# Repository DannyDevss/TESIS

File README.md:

# TESIS — Workspace ROS 2 del UGV de rescate (RMD)

Workspace de **ROS 2 Jazzy** para un vehículo terrestre no tripulado (UGV) de
rescate con **orugas y flippers articulados**. Incluye el puente con el hardware
de motores, la odometría, la fusión sensorial (EKF), el modelo del robot (URDF)
y la inferencia de la política de flippers entrenada por refuerzo en el PC.

```bash
cd ~/TESIS && git checkout PRINCIPAL
colcon build --packages-select ugv_bridge && source install/setup.bash
ros2 launch ugv_bridge can_studio.launch.py   # simulación CAN + espía + Foxglove
```

Después, conectar Foxglove a `ws://localhost:8765` y cargar el layout
`src/ugv_bridge/config/ugv_control_v4.json`. **Foxglove es la única interfaz**:
no hay RViz ni ventanas Qt en ningún launch.

## Paquete (`src/`)

| Paquete | Rol | Ejecutables |
|---------|-----|-------------|
| **ugv_bridge** | Todo: puente ROS ↔ motores (orugas + flippers), IMU, odometría, EKF, URDF, launch, espía del bus CAN e inferencia de la política | `flipper_node`, `track_odometry_node`, `teleop_flippers`, `can_monitor`, `politica_flippers`, `motor_emulator`, `pi3hat_imu`, `esp32_bridge`, `gui_a_comandos` *(legado)* |

**Un solo paquete, a propósito.** El workspace tenía además `ugv_core`,
`ugv_sim`, `ugv_policy` y `ugv_msgs`, de una versión anterior del proyecto que
modelaba navegación 2D plana: telémetros, `/cmd_vel` y tres acciones discretas.
Esa no es la tarea de la tesis. Este robot tiene orugas y flippers articulados
y se comanda por `/cmd_tracks` y `/cmd_flippers`, y no había nada que conectara
lo uno con lo otro. Se eliminaron en octubre de 2026 para que no quedara código
muerto con apariencia de sistema. Lo único que se rescató de ellos es la
inferencia de la política, que ahora vive en `ugv_bridge`.

## Arquitectura del track de flippers (`ugv_bridge`)

```
Foxglove (paneles Publish y Teleop)  /  política RL
   │  /cmd_tracks (vel. orugas)   /cmd_flippers (pos. flippers)
   ▼
flipper_node  ──►  RMD_Hardware (real pi3hat/CAN  o  gemelo digital)
   │  /joint_states   /imu/data_raw
   ├──► track_odometry_node ──► /odom ─┐
   │                                   ├──► EKF (robot_localization) ──► /odometry/filtered + TF
   └──► robot_state_publisher (URDF) ──► TF de cada flipper ──► Foxglove
```

- **8 motores**: IDs 1–4 orugas (comando de velocidad), IDs 5–8 flippers (comando de posición).
- **Flippers**: juntas `continuous`, giran **360°** sin topes.
- **Sim-to-real**: el mismo nodo sirve para simulación y hardware; solo cambia el
  parámetro `modo_simulacion`. El modo hardware real (pi3hat + CAN + IMU) queda como TODO.

## Geometría del robot: una sola fuente de verdad

Todas las dimensiones físicas (posición de los motores de flipper, largo del
flipper, radio de las ruedas, radio y separación de las orugas, montaje de la IMU)
viven en **[`src/ugv_bridge/config/geometria_robot.yaml`](src/ugv_bridge/config/geometria_robot.yaml)**.
De ahí las leen, sin duplicar un solo número:

```
config/geometria_robot.yaml          <-- editar SOLO aquí
        |
        +--> urdf/ugv.urdf.xacro     (xacro.load_yaml)  --> modelo 3D, colisiones, TF
        +--> track_odometry_node     (radio/ancho de orugas)
        +--> flipper_node / driver   (IMU sintética, montaje de la IMU)
```

Cuando lleguen las medidas reales del chasis:

```bash
# 1. Editar config/geometria_robot.yaml
# 2. Refrescar el URDF plano (para Foxglove y herramientas que no procesan xacro)
bash src/ugv_bridge/scripts/generar_urdf.sh
# 3. Recompilar
colcon build
```

Los launch procesan el `.xacro` en caliente, así que el modelo **nunca** queda
desfasado del YAML. El `.urdf` plano es un artefacto generado: no editarlo a mano.

## Compilar

```bash
cd ~/Proyectos/ugv_ws
colcon build
source install/setup.bash
```

## Uso rápido

> **La única interfaz es Foxglove.** Ningún launch abre RViz ni ventanas Qt: la
> GUI de sliders y la vieja ventana de `can_monitor` publicaban en los mismos
> tópicos de comando que Foxglove y se pisaban entre sí (`flipper_node` retiene
> el último comando que recibe). Todos los launch levantan el puente WebSocket
> en el 8765; conecta con `ws://localhost:8765` y el layout
> `config/ugv_control_v4.json`.

```bash
# Posar el robot (gemelo digital), sin locomoción:
ros2 launch ugv_bridge view.launch.py

# Sistema completo (driver + odometría + EKF + Foxglove):
ros2 launch ugv_bridge flipper.launch.py use_ekf:=true

# Simulación con tramas CAN reales sobre vcan0, y con espía del bus:
ros2 launch ugv_bridge can_view.launch.py
ros2 launch ugv_bridge can_studio.launch.py

# Matar ventanas/publicadores huérfanos de una sesión vieja:
bash src/ugv_bridge/scripts/limpiar_fantasmas.sh

# Mover (un solo mensaje basta; el nodo retiene el último comando):
ros2 topic pub --once /cmd_flippers std_msgs/msg/Float64MultiArray "{data: [0.78,0.78,0.78,0.78]}"
ros2 topic pub --once /cmd_tracks   std_msgs/msg/Float64MultiArray "{data: [5.0,5.0,5.0,5.0]}"

# Política de flippers, solo observando las señales táctiles (no comanda nada):
ros2 launch ugv_bridge flipper.launch.py use_politica:=true
```

> ⚠️ Usa `--once`, no `-r`. La velocidad de las orugas es persistente: para frenar,
> publica explícitamente `[0,0,0,0]` en `/cmd_tracks`.

## RL: se entrena en el PC, se ejecuta en la Raspberry

El entrenamiento **no** corre en la Pi. En el robot solo va un archivo `.onnx`
ya entrenado, que ejecuta `politica_flippers` con `onnxruntime`. La Pi no
necesita gymnasium, ni stable-baselines3, ni torch.

```
PC de alta gama                          Raspberry Pi
---------------                          ------------
simulador + RL (PPO/SAC)                 politica_flippers
        |                                  lee /joint_states, /imu/data_raw
        v                     .onnx        construye la observación
scripts/exportar_onnx.py  ──────────────▶  ejecuta la red (onnxruntime)
                          .json            publica /cmd_flippers y /cmd_tracks
```

La política la entrena un profesor y es **autónoma**: maneja flippers y orugas.
Su **contrato** (qué es cada número que entra y sale de la red) viaja en el
`.json` junto al modelo, y el robot arma la observación a partir de él: así no
puede desincronizarse con el simulador. El formato está en
`ugv_bridge/contrato_politica.py`; los frenos (desactivada al arrancar,
watchdog, topes duros y parada segura con orugas a 0), en
`ugv_bridge/ejecutor_politica.py`. Para probar sin modelo real:
`scripts/modelo_falso.py`.

Detalle completo del objetivo (percepción táctil sin sensor táctil), de las
señales y de los frenos de seguridad en `COMO_EJECUTAR.md`, sección 3.

## Documentación

- **[COMO_EJECUTAR.md](COMO_EJECUTAR.md)** — runbook detallado (entornos, launch, tópicos, inspección).
- **[DEFENSA_ROS2.txt](DEFENSA_ROS2.txt)** — guía de preguntas/respuestas de ROS 2 para la defensa.
- **[BITACORA_2026-07-11.txt](BITACORA_2026-07-11.txt)** — bitácora de construcción del track de flippers.

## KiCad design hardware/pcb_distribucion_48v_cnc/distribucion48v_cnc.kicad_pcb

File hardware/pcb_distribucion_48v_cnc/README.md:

# Distribución de 48 V — versión para la CNC del laboratorio

El circuito es el mismo de [`../pcb_distribucion_48v`](../pcb_distribucion_48v/README.md):
XT60 de batería, 8 salidas XT30 con fusible 5×20, una salida auxiliar de 48 V con
fusible y sensado con PTC. Cambia el cobre, para poder
fresarla en la **Bungard CCD** del laboratorio (manual en `../CNCFABLAB/`).

## Qué cambia respecto de la placa para fabricante

| | Fabricante (`pcb_distribucion_48v`) | CNC (esta) |
|---|---|---|
| Caras de cobre | 2 (48 V arriba, GND abajo) | **1, la de abajo (lado de soldadura)** |
| Cobre | 2 oz (70 µm) | **1 oz (35 µm)**, el de las placas vírgenes comunes |
| Metalizado de agujeros | sí | **no**: la CCD no metaliza |
| Serigrafía / máscara | sí | no; los rótulos `M1`…`M8` van fresados en el cobre |
| Taladro de los clips | 1.3 mm | **1.4 mm**, el mismo de las borneras: una broca menos |
| Tamaño, agujeros M3 | 104 × 84 mm | igual: se atornilla en el mismo lugar |

**Por qué una sola cara:** sin metalizado, un pad solo conecta en la cara donde se
suelda. Los XT60 y XT30 van verticales con el cuerpo apoyado en la cara de arriba, así
que un pad de arriba quedaría tapado y no se podría soldar. Todo el cobre va abajo,
donde se sueldan todas las patas.

**Cómo entra en una cara:** GND rellena todo lo que no es otra red. Queda un anillo
por el borde que toca los `-` del XT60, de los ocho XT30 y de las borneras. Adentro
van el bus de 48 V (franja central), los planos `OUT1`…`OUT8` (uno por canal, del
fusible al `+` de su XT30), el plano `AUX48V` (de F10 a J11, igual que un canal más) y
la pista de sensado (del PTC a J10). Nada se cruza. El DRC da **0 sin conectar**.

## Archivos

| Archivo | Qué es |
|---|---|
| `fabricacion/distribucion48v_cnc-B_Cu.gbl` | Cobre (cara **de abajo**). Gerber RS-274X, sin atributos X2. |
| `fabricacion/distribucion48v_cnc-Edge_Cuts.gm1` | Contorno de la placa. |
| `fabricacion/distribucion48v_cnc.drl` | Taladros, Excellon en mm, un solo archivo (64 agujeros, 5 diámetros). |
| `montaje_1a1.pdf` | Vista de arriba a **escala 1:1**: para imprimir y comprobar los conectores. |
| `preview.png` | Cara de arriba con el cobre de abajo visto por transparencia. |
| `cobre_lado_soldadura.png` | El cobre visto desde abajo, como queda la placa fresada. |
| `gen.py` | Fuente: `python3 gen.py` regenera todo. |
| `centrar_pdf.py` | Centra la placa en `montaje_1a1.pdf` (kicad-cli la deja en la esquina). |

Los componentes son los mismos de la otra placa: ver su `bom.csv` y `COMPRAS.md`.
Además hace falta **una placa virgen FR4 de 1.6 mm, una cara, 35 µm**, de al menos
125 × 95 mm. La Eurocard de 160 × 100 sirve, y sobra espacio para un intento más.

## En la CCD, paso a paso

Basado en el manual de la Bungard CCD (RoutePro3000). Los números de página son los
del manual.

### 1. Poner la placa

- **Cobre hacia arriba.** La fresa trabaja desde arriba. Los componentes van después
  en la otra cara, la sin cobre.
- Debajo, una **placa de sacrificio** (MDF o la "drill backing board" del
  laboratorio) más grande que la virgen, fija a la mesa con las bridas. Así las
  brocas y la fresa de contorno la atraviesan sin tocar la mesa de aluminio (p. 24).
- La placa virgen va pegada a la de sacrificio con **cinta doble faz**, bien plana y
  sin burbujas. Con una sola cara no hacen falta pines de referencia (p. 24–25). Si
  la placa se curva, la aislación sale más honda en unas partes que en otras.
- Ubicarla a unos **5 mm del cero de la máquina**, en la esquina de adelante a la
  izquierda, con un borde alineado con el eje X o Y (p. 17 y 20).
- En el software, cargar el **espesor real** de la placa (1.6 mm) y el de la de
  sacrificio (p. 20).

### 2. Cargar los archivos

En RoutePro3000/IsoCam: el `.drl` como taladros, el `B_Cu.gbl` como **capa de abajo**
y el `Edge_Cuts.gm1` como contorno. El gerber está visto desde arriba, como todo
gerber: al marcarlo como capa de abajo, el software lo espeja. **Comprobar en
pantalla que los rótulos `M1`…`M8` se leen al derecho en la vista de abajo**: si se
leen espejados, la placa sale al revés.

### 3. Fresar, y cuándo cambiar de herramienta

Son **5 herramientas** y se usan en este orden (p. 21). Cada fila es un cambio: se
termina todo lo de esa herramienta antes de pasar a la siguiente.

| Cuándo | Herramienta | Qué hace |
|---|---|---|
| 1. Al empezar, capa de taladros | broca **0.8 mm** | los 2 agujeros del PTC (F9) |
| 2. Cuando termina la 0.8 | broca **1.4 mm** | los 40 agujeros de clips y borneras |
| 3. Cuando termina la 1.4 | broca **2.7 mm** | los 16 agujeros de los XT30 |
| 4. Terminados los taladros, se cambia a la capa de aislación | fresa de aislación **0.5 mm** (o la V que tengan) | separa las redes en el cobre |
| 5. Terminada la aislación, se cambia a la capa de contorno | fresa de contorno **2.0 mm** | XT60 (4.5 mm) y M3 (3.2 mm) como círculos, y al final el borde de la placa con puentes |

Cómo se hace cada cambio depende de la máquina:

- **Con cambiador automático (ATC)**, la barra de portaherramientas al frente:
  antes de empezar se ponen las 5 herramientas en los puestos que pide el software,
  con el **puesto 0 libre** para el pin de prueba. Al dar Start, la máquina mide
  cada una y las cambia sola (p. 19–21).
- **Manual (MTC o sin cambiador):** al terminar con una herramienta, el eje Z sube y
  el software pide la siguiente. Se cambia **con el husillo detenido**: apretar el
  botón de arriba del husillo, girar hasta que trabe, soltar la pinza (p. 19). Después
  de poner la nueva, OK.

En cualquiera de los dos casos:

- **Todas las herramientas con el anillo de tope** a 21 mm de la punta (p. 11). Con
  él la máquina sabe el largo; sin él, puede clavar la herramienta en la mesa.
- **No tocar la herramienta con el husillo girando**; esperar a que se detenga (p. 9).
- **Para la aislación, el limitador de profundidad** (el patín verde alrededor de la
  fresa): corta siempre lo justo aunque la placa no esté perfecta (p. 21–22).
  Con ATC, la abertura del patín mira hacia los portaherramientas; si no, choca en
  el cambio (p. 22).
- **Antes de la aislación completa, probar la profundidad** en un trazo que no
  importe, por ejemplo el contorno exterior, como sugiere el manual: tiene que
  cortar el cobre y apenas marcar la fibra. Si queda cobre, bajar el limitador un
  punto (cada punto son 50 µm). Mejor que quede alto que hondo (p. 22).

### 4. Después de fresar

Antes de soldar, con el multímetro en continuidad, medir que **no** suene entre GND,
VBAT, AUX48V, SENSE y cada OUT. Una rebaba o una tira de cobre que no se fresó deja un corto a
48 V.

### Herramientas y parámetros (FR4, tablas del manual)

| Paso | Herramienta | Diámetro | Avance XY | RPM | Avance Z | Página |
|---|---|---|---|---|---|---|
| Taladro (PTC, 2) | broca estándar | 0.8 mm | 2200 mm/min | 63 000 | — | 29 |
| Taladro (clips y borneras, 40) | broca estándar | 1.4 mm | 2800 mm/min | 63 000 | — | 29 |
| Taladro (XT30, 16) | broca estándar | 2.7 mm | 1800 mm/min | 45 400 | — | 29 |
| Agujeros M3 (3.2 mm, 4) y XT60 (4.5 mm, 2) | ver abajo | | | | | 29 |
| Aislación | fresa de un filo (micro cutter) | 0.5 mm | 100–200 mm/min | 63 000 | 200 mm/min | 31 |
| Contorno | fresa SC/FT | 2.0 mm | 1000 mm/min | 38 800 | 1300 mm/min | 32 |

- **Agujeros de más de 3 mm:** el manual recomienda pretaladrar con 1.7 mm desde
  3.0 mm. Con el diámetro máximo recomendado de 3.175 mm, lo más simple es que
  RoutePro/IsoCam los **frese como círculo** con la fresa de contorno. Si el
  laboratorio tiene broca de 3.2 y de 4.5, también sirve.
- **Ancho de aislación: 1 mm.** Las redes están separadas 1 mm en el diseño. Para
  48 V sin barniz, IPC-2221 pide **al menos 0.6 mm**: una sola pasada de una fresa
  de 0.2–0.4 mm **no alcanza**. Pedir en IsoCam un ancho de aislación de 1 mm, por
  ejemplo dos pasadas de 0.5 mm, o una fresa de 1 mm.
- **Contorno con puentes** (p. 25) para que la placa no salte al final del corte.

## Corriente con cobre de 1 oz

Anchos en el punto más estrecho. Capacidad según IPC-2221, capa externa, con 20 °C de
subida de temperatura.

| Tramo | Ancho | Aguanta | Lleva (motores a ~3 A) |
|---|---|---|---|
| Plano por canal `OUTn` | 5 mm (junto al `-` del XT30) | ~10 A | 3 A (6 A nominal del driver) |
| Franja de GND arriba / abajo | 8.5 mm | ~15 A | 4 canales: ~12 A |
| Bus de 48 V | 21 mm | ~29 A | 8 canales: ~24 A |

Alcanza para lo que se pidió, con poco margen en las franjas de GND. Si se quiere más
margen, o si el cobre se oxida: **estañar** el bus, las franjas de GND y los planos
`OUT` (una capa de estaño suma sección), o soldar encima un alambre de cobre de
1.5 mm² a lo largo del bus y de las franjas.

## Después de fresar

- **No tiene máscara**: el cobre queda al aire. Estañarlo o pasarle barniz (laca
  para PCB, en spray) después de soldar. El barniz además mejora la aislación de 48 V.
- **Rótulos**: los `M1`…`M8`, `AUX` (salida de 48 V, J11) y `SEN` (sensado, J10) en
  cobre se leen desde abajo. Arriba no hay
  serigrafía: marcar con plumón permanente los IDs de motor junto a cada XT30, y
  `+`/`-` en el XT60 y las borneras, usando `montaje_1a1.pdf` de guía.
- Los pads de potencia van **sin thermal relief**, conectados de lleno al plano: se
  sueldan con un cautín de 60–80 W y punta gruesa. Con 1 oz cuesta menos que con
  2 oz.
- Al soldar los XT30/XT60, que el cuerpo quede **apoyado y recto** sobre la placa:
  sin metalizado, el pad de cobre es lo único que sujeta la pata. Si se
  tira del cable, se puede levantar el pad. Asegurar los cables con amarras al chasis.

## Antes de ir al laboratorio

- [ ] **Polaridad de los XT** (sigue pendiente, ver `../pcb_distribucion_48v/PENDIENTES.md`):
      imprimir `montaje_1a1.pdf` **al 100 %, sin "ajustar a la página"**, medir que
      la placa mida 104 × 84 mm en el papel, y poner encima un XT60 y un XT30 reales:
      el `-` moldeado en el cuerpo tiene que caer en el pad marcado `-`.
- [ ] Con el mismo papel, comprobar que las patas de los **clips 445-030** caen en los
      agujeros (dos patas a 5.2 mm, clip a clip 20.5 mm).
- [ ] Preguntar en el laboratorio:
  - ¿Tienen **placa virgen de una cara**? Si solo hay de doble cara, el cobre de
        arriba tiene que salir entero, o por lo menos fresar un anillo alrededor de
        cada agujero. Si no, las patas de los conectores tocan ese cobre y quedan
        todas en corto entre sí.
  - ¿Qué **fresas y brocas** hay en el cambiador? Hacen falta las brocas de 0.8,
        1.4 y 2.7 mm, una fresa de aislación (0.5 mm o un V-cut) y una fresa de
        contorno de 2 mm.
  - ¿Usan **IsoCam** para generar la aislación desde el gerber?

## Regenerar

Necesita KiCad 10 (la API `pcbnew` de Python):

```
python3 gen.py
kicad-cli pcb drc --refill-zones --severity-all distribucion48v_cnc.kicad_pcb
kicad-cli pcb export gerbers --layers B.Cu,Edge.Cuts --no-x2 --no-netlist -o fabricacion/ distribucion48v_cnc.kicad_pcb
kicad-cli pcb export drill --format excellon --excellon-units mm --excellon-zeros-format decimal --drill-origin absolute -o fabricacion/ distribucion48v_cnc.kicad_pcb
kicad-cli pcb export pdf --layers F.Silkscreen,F.Fab,Edge.Cuts --mode-single --sp --black-and-white -o montaje_1a1.pdf distribucion48v_cnc.kicad_pcb
python3 centrar_pdf.py      # mueve la placa al centro del A4, sin cambiar la escala
```

Estado al generarla: DRC de KiCad 10.0.7 con **0 sin conectar** y 0 errores de
cobre. Quedan 36 avisos `silk_over_copper` (serigrafía sobre pads): no importan,
porque la CCD no imprime serigrafía.

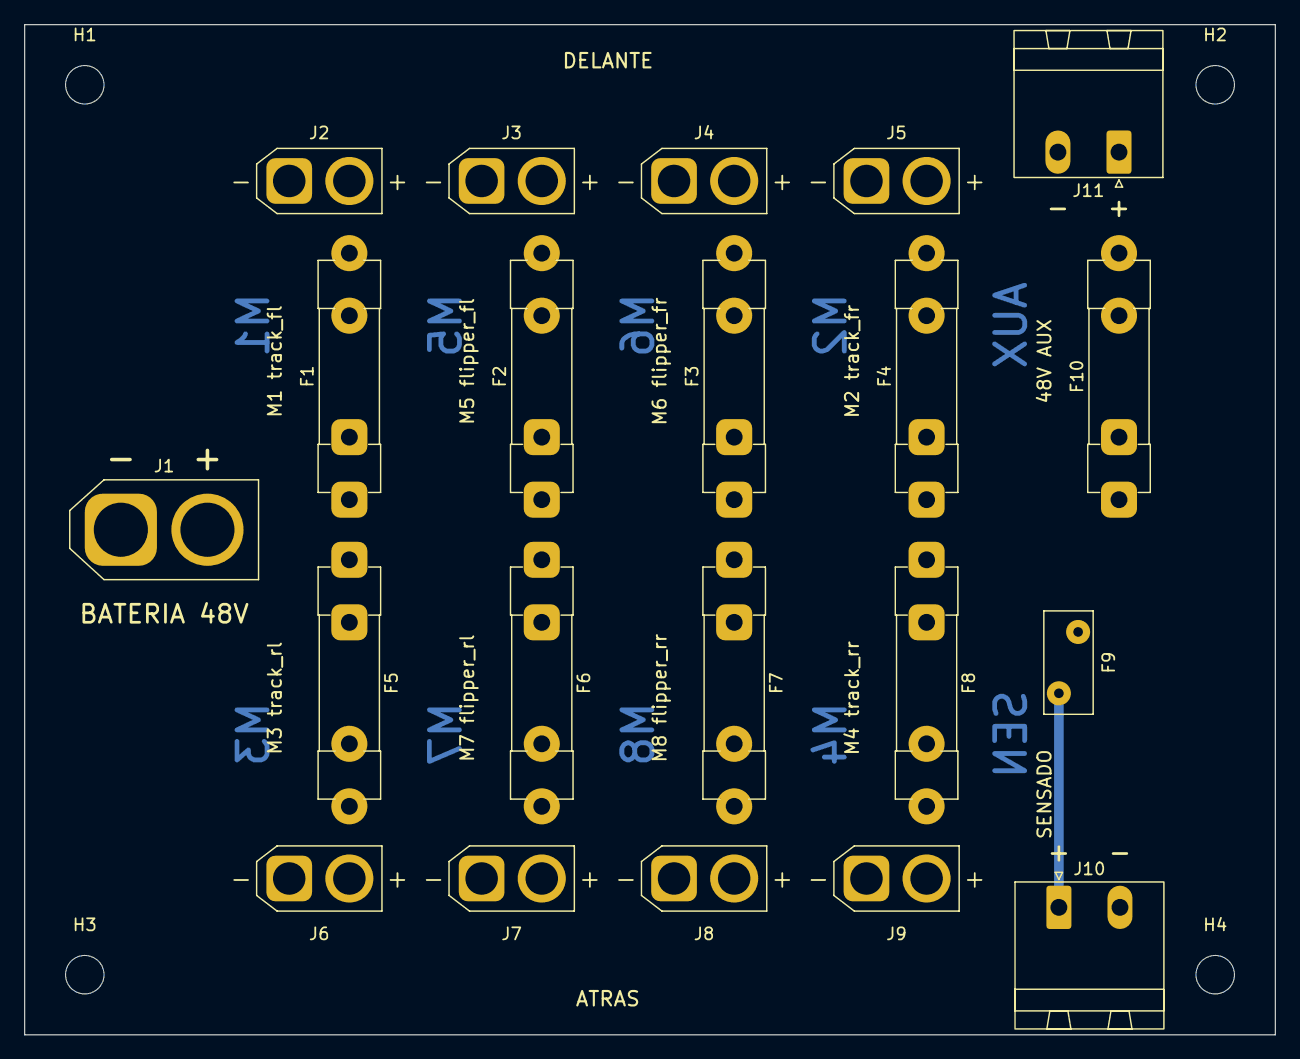
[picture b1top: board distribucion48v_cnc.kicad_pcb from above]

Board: 2 copper layers, 104.0 x 84.0 mm, 25 parts (0 on the bottom side), 12 nets.

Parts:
F1, F2, F3, F4, F5, F6, F7, F8: T10A 5x20; Fuseholder_Clip-5x20mm_Littelfuse_445-030_Inline_P20.50x5.2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
F9: 0ZRE0005FF; Fuse_BelFuse_0ZRE0005FF_L8.3mm_W3.8mm
F10: T2A 5x20; Fuseholder_Clip-5x20mm_Littelfuse_445-030_Inline_P20.50x5.2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
H1, H2, H3, H4: M3; MountingHole_3.2mm_M3
J1: XT60-M; AMASS_XT60-M_1x02_P7.20mm_Vertical
J2, J3, J4, J5, J6, J7, J8, J9: XT30U-F; AMASS_XT30U-F_1x02_P5.0mm_Vertical
J10: SENSADO; PhoenixContact_MSTBA_2,5_2-G-5,08_1x02_P5.08mm_Horizontal
J11: 48V AUX; PhoenixContact_MSTBA_2,5_2-G-5,08_1x02_P5.08mm_Horizontal

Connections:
AUX48V: F10.2, J11.1
GND: J1.1, J2.1, J3.1, J4.1, J5.1, J6.1, J7.1, J8.1, J9.1, J10.2, J11.2
OUT1: F1.2, J2.2
OUT2: F2.2, J3.2
OUT3: F3.2, J4.2
OUT4: F4.2, J5.2
OUT5: F5.2, J6.2
OUT6: F6.2, J7.2
OUT7: F7.2, J8.2
OUT8: F8.2, J9.2
SENSE: F9.2, J10.1
VBAT: F1.1, F2.1, F3.1, F4.1, F5.1, F6.1, F7.1, F8.1, F9.1, F10.1, J1.2

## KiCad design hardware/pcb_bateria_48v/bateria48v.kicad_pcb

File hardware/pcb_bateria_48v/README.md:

# Medidor de batería 48 V — ESP32-S3-WROOM-1

Placa de 2 capas, 110 × 80 mm: divisor de tensión a GPIO4, buzzer pasivo y 3 LEDs.

**Todo es pasante (through-hole)** menos el módulo, que sólo existe en SMD.
Resistencias axiales de 1/4 W a paso 10.16 mm, cerámicos de disco, electrolíticos
radiales, LEDs de 5 mm, TO-92 y TO-220. Soldable a mano sin lupa.

## Archivos

| Archivo | Qué es |
|---|---|
| `bateria48v.kicad_pcb` | La placa. **Footprints embebidos**: abre sin instalar librerías. |
| `bateria48v.kicad_dru` | Reglas DRC propias para la sección de 48 V. |
| `preview.png` / `preview.svg` | Vista previa del ruteo. |
| `bom.csv`, `netlist.txt`, `pinout.txt` | Lista de materiales, netlist y asignación de pines. |
| `design.py`, `place.py`, `routes.py`, `fp_lib.py` | Fuente paramétrica: cambias un número y regeneras. |
| `gen.py`, `drc.py`, `verify.py`, `check_place.py` | Generador y verificadores. |
| `PENDIENTES.md` | Lo que falta por hacer antes de fabricar. |

Regenerar todo: `python3 gen.py && python3 drc.py && python3 verify.py`

## Lo primero que tienes que decidir

**El divisor 180k/10k satura el ADC si tu pack pasa de ~55 V.**

Ganancia = 10k/190k = 1/19. Con atenuación de 12 dB el ADC del S3 llega a ~3.1 V
pero deja de ser lineal por encima de ~2.8 V:

| Batería | V en GPIO4 | Estado |
|---|---|---|
| 13S Li-ion vacía (39 V) | 2.053 V | bien |
| 13S nominal (48.1 V) | 2.532 V | bien |
| **13S llena (54.6 V)** | **2.874 V** | en el borde de la zona lineal |
| 15S LiFePO4 llena (54.75 V) | 2.882 V | en el borde |
| **16S LiFePO4 llena (58.4 V)** | **3.074 V** | **satura, lectura inservible** |

- Si tu pack es **13S Li-ion o 15S LiFePO4**: 180k/10k funciona, con poco margen arriba.
- Si es **16S LiFePO4** o quieres margen: pon **R1 = 220k** (ganancia 1/23 → 58.4 V da 2.54 V).
  La huella es la misma, es cambiar el componente.

Dejé 180k/10k como valor por defecto porque es lo que pediste.

## Antes de mandar a fabricar

1. **Contrasta el footprint del módulo con el datasheet de Espressif.** No tenía KiCad
   ni acceso al PDF, así que reconstruí las cotas (18 × 25.5 mm, paso 1.27 mm,
   pads 0.9 × 2.0 mm, 15 + 10 + 15 castellados + pad térmico) y las dejé como
   constantes al principio de `fp_lib.py`. Si alguna no cuadra, la cambias ahí y
   corres `python3 gen.py`: se regenera la placa entera.
   Es lo único SMD de la placa; el resto son taladros de 0.9 mm con pad de 1.8 mm.
2. Abre el `.kicad_pcb`, pulsa **B** para rellenar los planos de GND y corre el
   **DRC de KiCad**. Mi verificador comprueba separaciones y conectividad, pero no
   sustituye al de KiCad (anillos de vía, islas de cobre aisladas, máscara).
3. Carga `bateria48v.kicad_dru` en *Rules → Custom Rules* para la regla de 1 mm en 48 V.

## Tres piezas que no existen en pasante

Al pasar todo a through-hole hubo que sustituir:

| Antes (SMD) | Ahora (pasante) | Por qué |
|---|---|---|
| BAT54S (doble diodo en SOT-23) | **D5A + D5B**, dos 1N4148 en DO-35 | el doble diodo en serie sólo viene en SOT-23 |
| MMBT2222A (SOT-23) | **2N3904** en TO-92 | mismo transistor, encapsulado pasante |
| AMS1117-3.3 (SOT-223) | **LM1117T-3.3** en TO-220 | vertical, 1=GND 2=VOUT 3=VIN |

Ojo con las patillas: el **2N3904 en TO-92 es E-B-C** mirando la cara plana de frente.
Los pads llevan la marca en serigrafía, pero confírmalo con tu datasheet porque hay
TO-92 con el orden invertido.

En los polarizados el **pad cuadrado es el positivo / ánodo**: electrolíticos (C3, C4,
C6, C7), LEDs (pata larga) y la banda del cátodo en los diodos DO-35.

## Alimentación

La placa **no lleva el convertidor de 48 V a 5 V**. El único cobre que ve los 48 V es
el divisor, confinado en la franja central-inferior con 1 mm de separación.

- **J1** (bornera): sólo sensado de batería. BAT+ y GND.
- **J2** (bornera): entrada de **5 V** desde un DC-DC externo de 48→5 V (necesita uno
  con entrada de 60 V: XL7005, LM5164 o un ladrillo aislado; los mini-360 / MP1584
  no aguantan 48 V).
- **U2** (AMS1117-3.3) genera los 3.3 V a bordo.

Consumo parásito del divisor: 287 µA a 54.6 V ≈ 0.21 mAh/mes. Si la placa va a estar
meses desconectada, conviene un MOSFET que corte el divisor; no lo incluí.

## Conectores

- **J3 — programación** (1×6, 2.54 mm): `1:TXD0  2:RXD0  3:IO0  4:EN  5:3V3  6:GND`.
  Adaptador USB-UART de **3.3 V**. Ese orden está elegido para que las cuatro señales
  lleguen sin cruzarse; si lo cambias, hay que reruear.
- **J4 — jumper del buzzer**: en serie con los 3.3 V. Abierto = mudo, sin tocar firmware.

## Pines usados

| Función | GPIO | Pad | Nota |
|---|---|---|---|
| Sensado de batería | **IO4** | 4 | ADC1_CH3 — ADC1 sigue midiendo con WiFi activo |
| LED verde | IO38 | 31 | |
| LED ámbar | IO39 | 32 | MTCK por defecto |
| LED rojo | IO40 | 33 | MTDO por defecto |
| Buzzer (PWM) | IO21 | 23 | fila inferior, sale hacia el bloque del buzzer |

Usar IO39/IO40 deja sin JTAG por pines, pero el S3 tiene USB-Serial-JTAG integrado
(IO19/IO20), que es la vía habitual, así que no se pierde nada en la práctica.

Los LEDs van **activos en alto** (GPIO → 220 Ω → LED → GND), ~6 mA cada uno.
El buzzer es **pasivo**: necesita PWM (LEDC), no nivel continuo. Lo mueve un
MMBT2222A con diodo de recirculación.

## Firmware — lectura del ADC

```c
#include "esp_adc/adc_oneshot.h"
#include "esp_adc/adc_cali_scheme.h"

#define DIVISOR 19.0f      // (180k + 10k) / 10k

adc_oneshot_unit_handle_t adc;
adc_cali_handle_t cali;

void bat_init(void) {
    adc_oneshot_unit_init_cfg_t u = { .unit_id = ADC_UNIT_1 };
    adc_oneshot_new_unit(&u, &adc);
    adc_oneshot_chan_cfg_t c = { .atten = ADC_ATTEN_DB_12, .bitwidth = ADC_BITWIDTH_DEFAULT };
    adc_oneshot_config_channel(adc, ADC_CHANNEL_3, &c);     // GPIO4 = ADC1_CH3
    adc_cali_curve_fitting_config_t k = {
        .unit_id = ADC_UNIT_1, .chan = ADC_CHANNEL_3,
        .atten = ADC_ATTEN_DB_12, .bitwidth = ADC_BITWIDTH_DEFAULT };
    adc_cali_create_scheme_curve_fitting(&k, &cali);
}

float bat_volts(void) {
    int acc = 0, mv;
    for (int i = 0; i < 64; i++) {            // promediar: el nodo es de alta impedancia
        int raw; adc_oneshot_read(adc, ADC_CHANNEL_3, &raw); acc += raw;
    }
    adc_cali_raw_to_voltage(cali, acc / 64, &mv);
    return mv / 1000.0f * DIVISOR;
}
```

**Calibra con un multímetro.** La tolerancia de dos resistencias al 1 % ya da ±2 %
(±1 V a 48 V), y el ADC del ESP32 suma lo suyo. Mide la tensión real en J1 y la que
reporta el firmware, y ajusta `DIVISOR`. Con una sola constante corriges casi todo.

El filtro RC (R3 = 1 k con C2 = 100 nF) da ~1.6 kHz de corte; con 64 muestras
promediadas la lectura queda estable.

## Lo que no incluí

- Convertidor de 48 V a 5 V a bordo (va fuera, por J2).
- Conector USB-C: se programa por J3. El módulo tiene USB nativo en IO19/IO20 libres
  si lo quieres añadir.
- Corte del divisor por MOSFET para almacenamiento largo.
- Versión SMD: si alguna vez la quieres compacta, `fp_lib.py` conserva las huellas
  0805/SOT-23/SOT-223 de la primera versión.

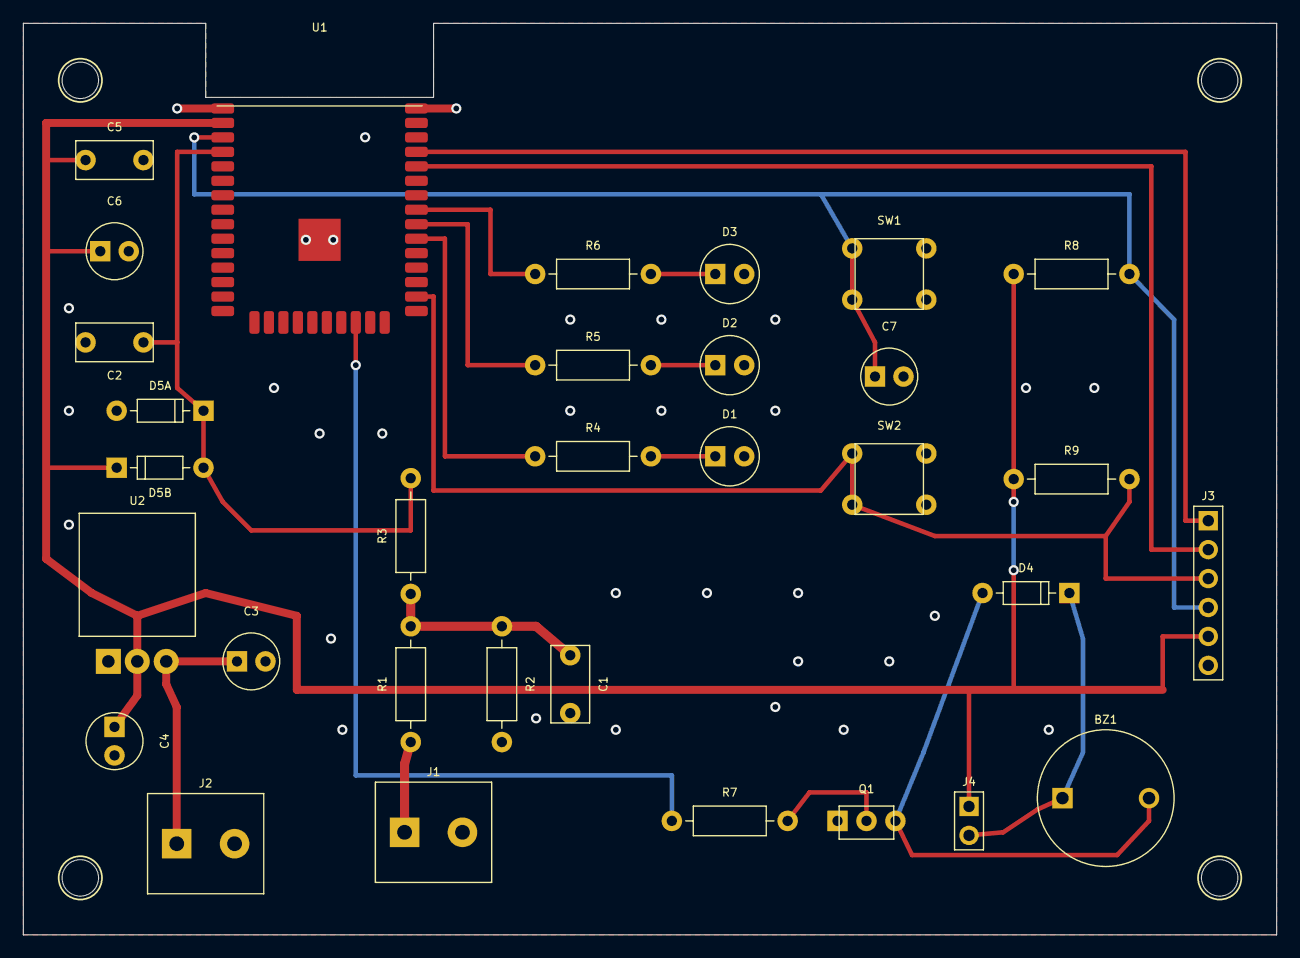
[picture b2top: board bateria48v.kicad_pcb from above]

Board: 2 copper layers, 110.0 x 80.0 mm, 32 parts (0 on the bottom side), 20 nets.

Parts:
BZ1: BUZZER; Buzzer_12x9.5RM7.6mm
C1, C2, C5: 100nF; C_Disc_P5.08mm
C3, C6: 10uF; CP_Radial_D5.0mm_P2.50mm
C4: 22uF; CP_Radial_D5.0mm_P2.50mm
C7: 1uF; CP_Radial_D5.0mm_P2.50mm
D1: VERDE; LED_D5.0mm
D2: AMBAR; LED_D5.0mm
D3: ROJO; LED_D5.0mm
D4, D5A, D5B: 1N4148; D_DO-35_P7.62mm
J1: BAT 48V; TerminalBlock_bornier-2_P5.08mm
J2: 5V IN; TerminalBlock_bornier-2_P5.08mm
J3: PROG; PinHeader_1x06_P2.54mm_Vertical
J4: BUZZER EN; PinHeader_1x02_P2.54mm_Vertical
Q1: 2N3904; TO-92_Inline
R1: 180k; R_Axial_DIN0207_P10.16mm
R2, R8, R9: 10k; R_Axial_DIN0207_P10.16mm
R3, R7: 1k; R_Axial_DIN0207_P10.16mm
R4, R5, R6: 220R; R_Axial_DIN0207_P10.16mm
SW1: RESET; SW_Tactile_6x6mm_THT
SW2: BOOT; SW_Tactile_6x6mm_THT
U1: ESP32-S3-WROOM-1
U2: LM1117T-3.3; TO-220-3_Vertical

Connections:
+3V3: C4.1, C5.1, C6.1, D5B.2, J3.5, J4.1, R8.1, R9.1, U1.2, U2.2
+5V: C3.1, J2.1, U2.3
AN_AMBAR: D2.1, R5.2
AN_ROJO: D3.1, R6.2
AN_VERDE: D1.1, R4.2
BAT+: J1.1, R1.1
BAT_ADC: C2.1, D5A.2, D5B.1, R3.2, U1.4
BAT_DIV: C1.1, R1.2, R2.1, R3.1
BUZZER_PWM: R7.1, U1.23
BZ_COL: BZ1.2, D4.1, Q1.3
BZ_PWR: BZ1.1, D4.2, J4.2
EN: C7.1, J3.4, R8.2, SW1.1, U1.3
GND: C1.2, C2.2, C3.2, C4.2, C5.2, C6.2, C7.2, D1.2, D2.2, D3.2, D5A.1, J1.2, J2.2, J3.6, Q1.1, R2.2, SW1.2, SW2.2, U1.1, U1.40, U1.41, U2.1
IO0: J3.3, R9.2, SW2.1, U1.27
LED_AMBAR: R5.1, U1.32
LED_ROJO: R6.1, U1.33
LED_VERDE: R4.1, U1.31
Q1_BASE: Q1.2, R7.2
RXD0: J3.2, U1.36
TXD0: J3.1, U1.37

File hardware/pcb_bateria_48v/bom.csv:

Ref,Valor,Huella,Descripcion,Nota
U1,ESP32-S3-WROOM-1,"modulo 18x25.5mm, 40 pads castellados 1.27mm",MCU + WiFi/BT,unico componente SMD: el modulo viene asi
U2,LM1117T-3.3 / LD1117V33,"TO-220 vertical, 3 pines 2.54mm","regulador 5V -> 3.3V, 800mA",1=GND 2=VOUT 3=VIN
J1,BAT SENSE,bornera 2 pines 5.08mm,entrada 48V a medir,"solo sensado, no alimenta"
J2,5V IN,bornera 2 pines 5.08mm,alimentacion 5V,desde DC-DC 48->5V externo
J3,PROG,header 1x6 2.54mm,1:TXD0 2:RXD0 3:IO0 4:EN 5:3V3 6:GND,adaptador USB-UART 3.3V
J4,BUZZER EN,jumper 1x2 2.54mm,habilita el buzzer,en serie con +3V3; abrir = mudo
R1,180k 1% 1/4W,"axial, paso 10.16mm",divisor rama alta,51.7V sobre ella a 54.6V
R2,10k 1% 1/4W,"axial, paso 10.16mm",divisor rama baja,usar 1% o mejor
R3,1k 1/4W,"axial, paso 10.16mm",serie de proteccion al ADC,limita la corriente al pin
R4,220R 1/4W,"axial, paso 10.16mm",limitador LED verde,
R5,220R 1/4W,"axial, paso 10.16mm",limitador LED ambar,
R6,220R 1/4W,"axial, paso 10.16mm",limitador LED rojo,
R7,1k 1/4W,"axial, paso 10.16mm",base de Q1,
R8,10k 1/4W,"axial, paso 10.16mm",pull-up EN,
R9,10k 1/4W,"axial, paso 10.16mm",pull-up IO0,
C1,100nF ceramico,"disco, paso 5.08mm",filtro sobre R2,polo con R1||R2 = 9.47k
C2,100nF ceramico,"disco, paso 5.08mm",filtro en el pin del ADC,cerca del pad 4
C3,10uF 25V,electrolitico radial D5mm,entrada del regulador,pata larga = +
C4,22uF 16V,electrolitico radial D5mm,salida del regulador,pata larga = +
C5,100nF ceramico,"disco, paso 5.08mm",desacople 3V3 del modulo,cerca del pad 2
C6,10uF 16V,electrolitico radial D5mm,reserva para picos de WiFi,pata larga = +
C7,1uF 16V,electrolitico radial D5mm,RC de arranque en EN,pata larga = + (al pin EN)
D1,LED verde 5mm,"LED 5mm, paso 2.54mm",estado OK,pata larga = anodo = pad cuadrado
D2,LED ambar 5mm,"LED 5mm, paso 2.54mm",aviso bateria media,pata larga = anodo
D3,LED rojo 5mm,"LED 5mm, paso 2.54mm",bateria baja,pata larga = anodo
D4,1N4148,"DO-35, paso 7.62mm",recirculacion del buzzer,banda = catodo = pad cuadrado
D5A,1N4148,"DO-35, paso 7.62mm",clamp del ADC contra GND,"anodo a GND, catodo al nodo"
D5B,1N4148,"DO-35, paso 7.62mm",clamp del ADC contra 3V3,"anodo al nodo, catodo a 3V3"
Q1,2N3904,"TO-92 en linea, paso 2.54mm",driver del buzzer,"1=E 2=B 3=C, cara plana hacia arriba"
SW1,RESET,tactil 6x6mm pasante,reset (EN),
SW2,BOOT,tactil 6x6mm pasante,modo descarga (IO0),
BZ1,buzzer pasivo 12mm,"TH 2 pines, paso 7.6mm","magnetico pasivo, 3.3V","necesita PWM, no DC"

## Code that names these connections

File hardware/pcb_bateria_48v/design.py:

# -*- coding: utf-8 -*-
"""
Definicion electrica de la placa: medidor de bateria 48V + buzzer + 3 LEDs
sobre ESP32-S3-WROOM-1.  Fuente unica de verdad para netlist, BOM y PCB.
"""

# ----------------------------------------------------------------------------
# Pinout del modulo ESP32-S3-WROOM-1 (40 pads castellados + pad termico 41)
# Distribucion fisica: pads 1..15 columna izquierda (arriba->abajo),
#                      pads 16..25 fila inferior (izq->der),
#                      pads 26..40 columna derecha (abajo->arriba),
#                      pad 41 = pad termico central (GND).
# ----------------------------------------------------------------------------
WROOM_PINS = {
     1: "GND",   2: "3V3",   3: "EN",    4: "IO4",   5: "IO5",
     6: "IO6",   7: "IO7",   8: "IO15",  9: "IO16", 10: "IO17",
    11: "IO18", 12: "IO8",  13: "IO19", 14: "IO20", 15: "IO3",
    16: "IO46", 17: "IO9",  18: "IO10", 19: "IO11", 20: "IO12",
    21: "IO13", 22: "IO14", 23: "IO21", 24: "IO47", 25: "IO48",
    26: "IO45", 27: "IO0",  28: "IO35", 29: "IO36", 30: "IO37",
    31: "IO38", 32: "IO39", 33: "IO40", 34: "IO41", 35: "IO42",
    36: "IO44", 37: "IO43", 38: "IO2",  39: "IO1",  40: "GND",
    41: "GND",
}

# Pines que NO se deben usar libremente
RESERVADOS = {
    3:  "EN  - reset",
    15: "IO3  - strapping (JTAG source)",
    16: "IO46 - strapping, solo entrada",
    26: "IO45 - strapping (VDD_SPI)",
    27: "IO0  - strapping (boot)",
    28: "IO35 - PSRAM octal en variantes R8",
    29: "IO36 - PSRAM octal en variantes R8",
    30: "IO37 - PSRAM octal en variantes R8",
    13: "IO19 - USB D-",
    14: "IO20 - USB D+",
    36: "IO44 - RXD0 consola",
    37: "IO43 - TXD0 consola",
}

# ----------------------------------------------------------------------------
# Asignacion de funciones  (pin_modulo -> (net, motivo))
# ----------------------------------------------------------------------------
ASIGNACION = {
     4: ("BAT_ADC",   "GPIO4 = ADC1_CH3. ADC1 sigue funcionando con WiFi activo."),
    31: ("LED_VERDE", "IO38 libre, sin strapping, en la columna derecha."),
    32: ("LED_AMBAR", "IO39 libre (MTCK por defecto, se pierde JTAG por pines)."),
    33: ("LED_ROJO",  "IO40 libre (MTDO por defecto)."),
    23: ("BUZZER_PWM","IO21 libre, en la fila inferior: sale hacia el bloque del buzzer."),
}

# ----------------------------------------------------------------------------
# Netlist: net -> lista de (referencia, pad)
# ----------------------------------------------------------------------------
NETS = {
    # --- alimentacion ---
    "GND": [("U1","1"),("U1","40"),("U1","41"),("J1","2"),("J2","2"),
            ("U2","1"),("C3","2"),("C4","2"),("C5","2"),("C6","2"),
            ("C1","2"),("C2","2"),("R2","2"),("D5A","1"),
            ("D1","2"),("D2","2"),("D3","2"),("Q1","1"),
            ("SW1","2"),("SW2","2"),("J3","6")],
    "+5V":  [("J2","1"),("U2","3"),("C3","1")],
    "BZ_PWR":[("J4","2"),("BZ1","1")],
    "+3V3": [("U1","2"),("U2","2"),("C4","1"),("C5","1"),("C6","1"),
             ("R8","1"),("R9","1"),("D5B","2"),("J3","5"),("J4","1")],

    # --- sensado de bateria 48V ---
    "BAT+":     [("J1","1"),("R1","1")],
    "BAT_DIV":  [("R1","2"),("R2","1"),("C1","1"),("R3","1")],
    "BAT_ADC":  [("R3","2"),("D5A","2"),("D5B","1"),("C2","1"),("U1","4")],

    # --- control ---
    "EN":       [("U1","3"),("R8","2"),("C7","1"),("SW1","1"),("J3","4")],
    "IO0":      [("U1","27"),("R9","2"),("SW2","1"),("J3","3")],
    "TXD0":     [("U1","37"),("J3","1")],
    "RXD0":     [("U1","36"),("J3","2")],

    # --- LEDs ---
    "LED_VERDE":[("U1","31"),("R4","1")],
    "LED_AMBAR":[("U1","32"),("R5","1")],
    "LED_ROJO": [("U1","33"),("R6","1")],
    "AN_VERDE": [("R4","2"),("D1","1")],
    "AN_AMBAR": [("R5","2"),("D2","1")],
    "AN_ROJO":  [("R6","2"),("D3","1")],

    # --- buzzer ---
    "BUZZER_PWM":[("U1","23"),("R7","1")],
    "Q1_BASE":   [("R7","2"),("Q1","2")],
    "BZ_COL":    [("Q1","3"),("BZ1","2"),("D4","1")],
}
# conexiones que cierran nets ya definidas mas arriba
# (catodo del flyback a +5V, retorno de C7 a GND)
NETS["BZ_PWR"].append(("D4","2"))
NETS["GND"].append(("C7","2"))

# ----------------------------------------------------------------------------
# BOM
# ----------------------------------------------------------------------------
BOM = [
    # ref, valor, huella, descripcion, nota
    ("U1", "ESP32-S3-WROOM-1", "modulo 18x25.5mm, 40 pads castellados 1.27mm",
     "MCU + WiFi/BT", "unico componente SMD: el modulo viene asi"),
    ("U2", "LM1117T-3.3 / LD1117V33", "TO-220 vertical, 3 pines 2.54mm",
     "regulador 5V -> 3.3V, 800mA", "1=GND 2=VOUT 3=VIN"),
    ("J1", "BAT SENSE", "bornera 2 pines 5.08mm", "entrada 48V a medir", "solo sensado, no alimenta"),
    ("J2", "5V IN", "bornera 2 pines 5.08mm", "alimentacion 5V", "desde DC-DC 48->5V externo"),
    ("J3", "PROG", "header 1x6 2.54mm", "1:TXD0 2:RXD0 3:IO0 4:EN 5:3V3 6:GND", "adaptador USB-UART 3.3V"),
    ("J4", "BUZZER EN", "jumper 1x2 2.54mm", "habilita el buzzer", "en serie con +3V3; abrir = mudo"),
    ("R1", "180k 1% 1/4W", "axial, paso 10.16mm", "divisor rama alta", "51.7V sobre ella a 54.6V"),
    ("R2", "10k 1% 1/4W", "axial, paso 10.16mm", "divisor rama baja", "usar 1% o mejor"),
    ("R3", "1k 1/4W", "axial, paso 10.16mm", "serie de proteccion al ADC", "limita la corriente al pin"),
    ("R4", "220R 1/4W", "axial, paso 10.16mm", "limitador LED verde", ""),
    ("R5", "220R 1/4W", "axial, paso 10.16mm", "limitador LED ambar", ""),
    ("R6", "220R 1/4W", "axial, paso 10.16mm", "limitador LED rojo", ""),
    ("R7", "1k 1/4W", "axial, paso 10.16mm", "base de Q1", ""),
    ("R8", "10k 1/4W", "axial, paso 10.16mm", "pull-up EN", ""),
    ("R9", "10k 1/4W", "axial, paso 10.16mm", "pull-up IO0", ""),
    ("C1", "100nF ceramico", "disco, paso 5.08mm", "filtro sobre R2", "polo con R1||R2 = 9.47k"),
    ("C2", "100nF ceramico", "disco, paso 5.08mm", "filtro en el pin del ADC", "cerca del pad 4"),
    ("C3", "10uF 25V", "electrolitico radial D5mm", "entrada del regulador", "pata larga = +"),
    ("C4", "22uF 16V", "electrolitico radial D5mm", "salida del regulador", "pata larga = +"),
    ("C5", "100nF ceramico", "disco, paso 5.08mm", "desacople 3V3 del modulo", "cerca del pad 2"),
    ("C6", "10uF 16V", "electrolitico radial D5mm", "reserva para picos de WiFi", "pata larga = +"),
    ("C7", "1uF 16V", "electrolitico radial D5mm", "RC de arranque en EN", "pata larga = + (al pin EN)"),
    ("D1", "LED verde 5mm", "LED 5mm, paso 2.54mm", "estado OK", "pata larga = anodo = pad cuadrado"),
    ("D2", "LED ambar 5mm", "LED 5mm, paso 2.54mm", "aviso bateria media", "pata larga = anodo"),
    ("D3", "LED rojo 5mm", "LED 5mm, paso 2.54mm", "bateria baja", "pata larga = anodo"),
    ("D4", "1N4148", "DO-35, paso 7.62mm", "recirculacion del buzzer", "banda = catodo = pad cuadrado"),
    ("D5A","1N4148", "DO-35, paso 7.62mm", "clamp del ADC contra GND", "anodo a GND, catodo al nodo"),
    ("D5B","1N4148", "DO-35, paso 7.62mm", "clamp del ADC contra 3V3", "anodo al nodo, catodo a 3V3"),
    ("Q1", "2N3904", "TO-92 en linea, paso 2.54mm", "driver del buzzer", "1=E 2=B 3=C, cara plana hacia arriba"),
    ("SW1","RESET", "tactil 6x6mm pasante", "reset (EN)", ""),
    ("SW2","BOOT", "tactil 6x6mm pasante", "modo descarga (IO0)", ""),
    ("BZ1","buzzer pasivo 12mm", "TH 2 pines, paso 7.6mm", "magnetico pasivo, 3.3V", "necesita PWM, no DC"),
]
